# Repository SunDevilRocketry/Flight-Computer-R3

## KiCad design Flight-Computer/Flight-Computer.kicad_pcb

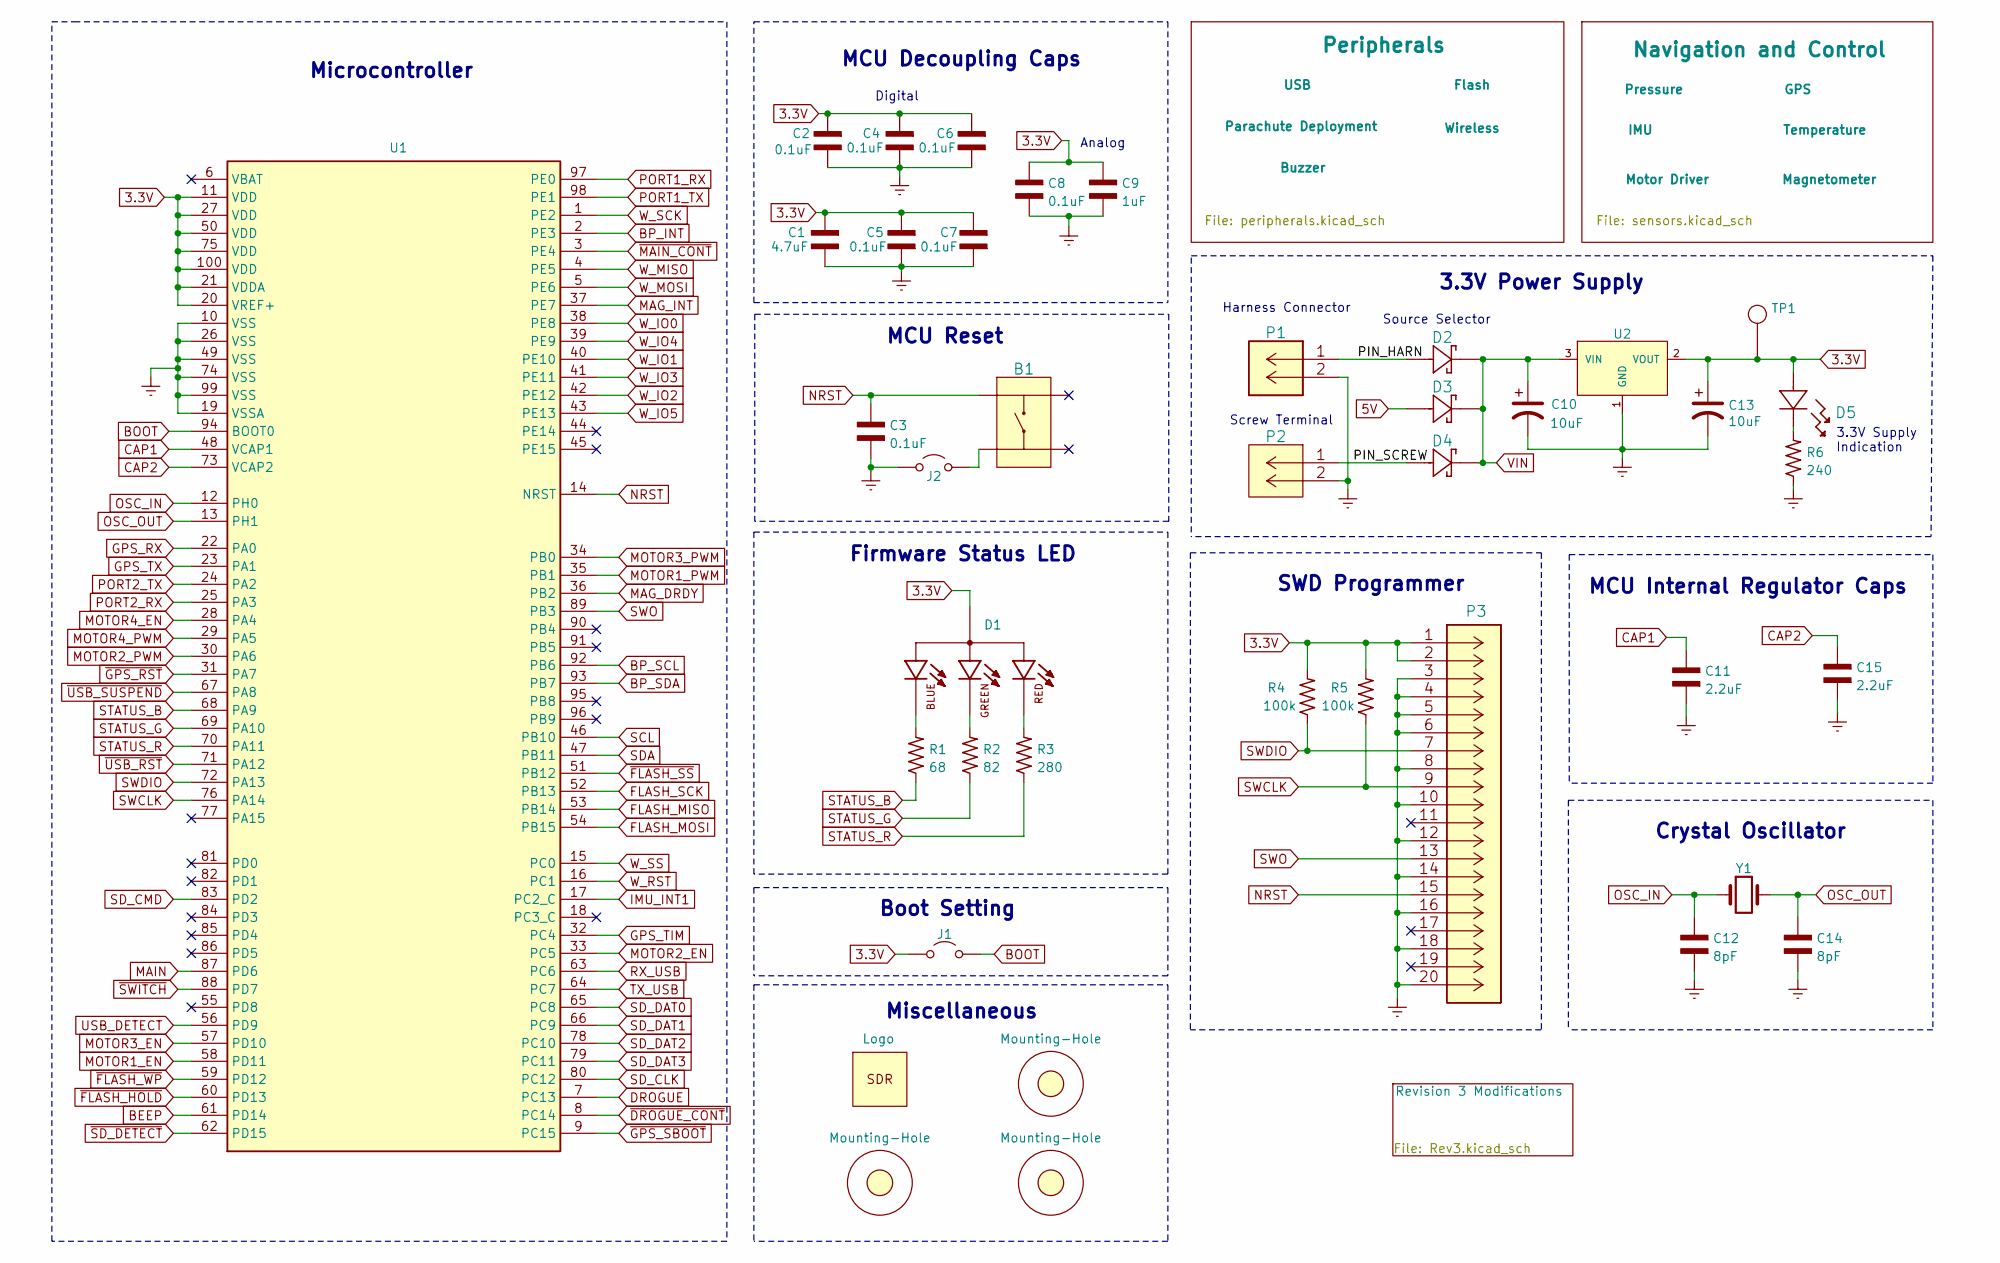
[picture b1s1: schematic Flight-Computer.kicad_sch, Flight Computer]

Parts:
B1: PTS647SM38SMTR2LFS
C1: 4.7uF; CAP_0603
C2, C3, C4, C5, C6, C7: 0.1uF; CAP_0603
C8: 0.1uF; C_0201_0603Metric
C9: 1uF; C_0201_0603Metric
C10, C13: 10uF; T491A106K010AT
C11, C15: 2.2uF; CAP_0603
C12, C14: 8pF; CAP_0603
D1: CLMVC-FKA-CL1D1L71BB7C3C3
D2, D3, D4: SM5819PL-TP
D5: SML-LX1206GC-TR
H1, H2, H3: Mounting-Hole; MountingHole_3mm
J1, J2: Jumper_NO; Jumper-NO
LOGO1: Logo
P1: 647676-2
P2: 1546551-2
P3: 3220-20-0200-00
R1: 68; RES_0603
R2: 82; RES_0603
R3: 280; RES_0603
R4, R5: 100k; RES_0603
R6: 240; RES_0603
TP1: TP
U1: STM32H750VBTx; STM32H750VBT6
U2: LMS8117AMP-3.3_NOPB; LMS8117AMP-3.3NOPB
Y1: ECS-240-18-33-JGN-TR

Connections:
3.3V: C1.1, C2.1, C4.1, C5.1, C6.1, C7.1, C8.1, C9.1, C13.1, D1.1, D5.2, J1.1 (A), P3.1, P3.2, R4.2, R5.2, TP1.1, U1.11 (VDD), U1.20 (VREF+), U1.21 (VDDA), U1.27 (VDD), U1.50 (VDD), U1.75 (VDD), U1.100 (VDD), U2.2 (VOUT); also elsewhere on the board
5V: D3.2; also elsewhere on the board
/PIN_HARN: D2.2, P1.1
/PIN_SCREW: D4.2, P2.1 (5)
BEEP: U1.61 (PD14); also elsewhere on the board
BOOT: J1.2 (B), U1.94 (BOOT0)
BP_INT: U1.2 (PE3); also elsewhere on the board
BP_SCL: U1.92 (PB6); also elsewhere on the board
BP_SDA: U1.93 (PB7); also elsewhere on the board
CAP1: C11.1, U1.48 (VCAP1)
CAP2: C15.1, U1.73 (VCAP2)
DROGUE: U1.7 (PC13); also elsewhere on the board
Earth: C1.2, C2.2, C3.2, C4.2, C5.2, C6.2, C7.2, C8.2, C9.2, C10.2, C11.2, C12.2, C13.2, C14.2, C15.2, J2.1 (A), P1.2, P2.2 (6), P3.3, P3.4, P3.5, P3.6, P3.8, P3.10, P3.12, P3.14, P3.16, P3.18, P3.20, R6.1, U1.10 (VSS), U1.19 (VSSA), U1.26 (VSS), U1.49 (VSS), U1.74 (VSS), U1.99 (VSS), U2.1 (GND); also elsewhere on the board
FLASH_MISO: U1.53 (PB14); also elsewhere on the board
FLASH_MOSI: U1.54 (PB15); also elsewhere on the board
FLASH_SCK: U1.52 (PB13); also elsewhere on the board
GPS_RX: U1.22 (PA0); also elsewhere on the board
GPS_TIM: U1.32 (PC4); also elsewhere on the board
GPS_TX: U1.23 (PA1); also elsewhere on the board
IMU_INT1: U1.17 (PC2_C); also elsewhere on the board
MAG_DRDY: U1.36 (PB2)
MAG_INT: U1.37 (PE7); also elsewhere on the board
MAIN: U1.87 (PD6); also elsewhere on the board
MOTOR1_EN: U1.58 (PD11); also elsewhere on the board
MOTOR1_PWM: U1.35 (PB1); also elsewhere on the board
MOTOR2_EN: U1.33 (PC5); also elsewhere on the board
MOTOR2_PWM: U1.30 (PA6); also elsewhere on the board
MOTOR3_EN: U1.57 (PD10); also elsewhere on the board
MOTOR3_PWM: U1.34 (PB0); also elsewhere on the board
MOTOR4_EN: U1.28 (PA4); also elsewhere on the board
MOTOR4_PWM: U1.29 (PA5); also elsewhere on the board
NRST: B1.3, C3.1, P3.15, U1.14 (NRST)
unnamed: D1.2, R1.2
unnamed: D1.3, R2.2
unnamed: D1.4, R3.2
unnamed: D5.1, R6.2
unnamed: B1.1, J2.2 (B)
OSC_IN: C12.1, U1.12 (PH0), Y1.1
OSC_OUT: C14.1, U1.13 (PH1), Y1.3
PORT1_RX: U1.97 (PE0); also elsewhere on the board
PORT1_TX: U1.98 (PE1); also elsewhere on the board
PORT2_RX: U1.25 (PA3); also elsewhere on the board
PORT2_TX: U1.24 (PA2); also elsewhere on the board
RX_USB: U1.63 (PC6); also elsewhere on the board
SCL: U1.46 (PB10); also elsewhere on the board
SDA: U1.47 (PB11); also elsewhere on the board
SD_CLK: U1.80 (PC12)
SD_CMD: U1.83 (PD2)
SD_DAT0: U1.65 (PC8)
SD_DAT1: U1.66 (PC9)
SD_DAT2: U1.78 (PC10)
SD_DAT3: U1.79 (PC11)
STATUS_B: R1.1, U1.68 (PA9)
STATUS_G: R2.1, U1.69 (PA10)
STATUS_R: R3.1, U1.70 (PA11)
SWCLK: P3.9, R5.1, U1.76 (PA14)
SWDIO: P3.7, R4.1, U1.72 (PA13)
SWO: P3.13, U1.89 (PB3)
TX_USB: U1.64 (PC7); also elsewhere on the board
USB_DETECT: U1.56 (PD9); also elsewhere on the board
VIN: C10.1, D2.1, D3.1, D4.1, U2.3 (VIN); also elsewhere on the board
W_IO0: U1.38 (PE8); also elsewhere on the board
W_IO1: U1.40 (PE10); also elsewhere on the board
W_IO2: U1.42 (PE12); also elsewhere on the board
W_IO3: U1.41 (PE11); also elsewhere on the board
W_IO4: U1.39 (PE9); also elsewhere on the board
W_IO5: U1.43 (PE13); also elsewhere on the board
W_MISO: U1.4 (PE5); also elsewhere on the board
W_MOSI: U1.5 (PE6); also elsewhere on the board
W_RST: U1.16 (PC1); also elsewhere on the board
W_SCK: U1.1 (PE2); also elsewhere on the board
W_SS: U1.15 (PC0); also elsewhere on the board
~DROGUE_CONT: U1.8 (PC14); also elsewhere on the board
~FLASH_HOLD: U1.60 (PD13); also elsewhere on the board
~FLASH_SS: U1.51 (PB12); also elsewhere on the board
~FLASH_WP: U1.59 (PD12); also elsewhere on the board
~GPS_RST: U1.31 (PA7); also elsewhere on the board
~GPS_SBOOT: U1.9 (PC15); also elsewhere on the board
~MAIN_CONT: U1.3 (PE4); also elsewhere on the board
~SD_DETECT: U1.62 (PD15)
~SWITCH: U1.88 (PD7); also elsewhere on the board
~USB_RST: U1.71 (PA12); also elsewhere on the board
~USB_SUSPEND: U1.67 (PA8); also elsewhere on the board

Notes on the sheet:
Crystal Oscillator
3.3V Power Supply
MCU Internal Regulator Caps
MCU Reset
Firmware Status LED
3.3V Supply Indication
Source Selector
MCU Decoupling Caps
Boot Setting
Miscellaneous
Analog
Screw Terminal
Microcontroller
Harness Connector
Digital
SWD Programmer

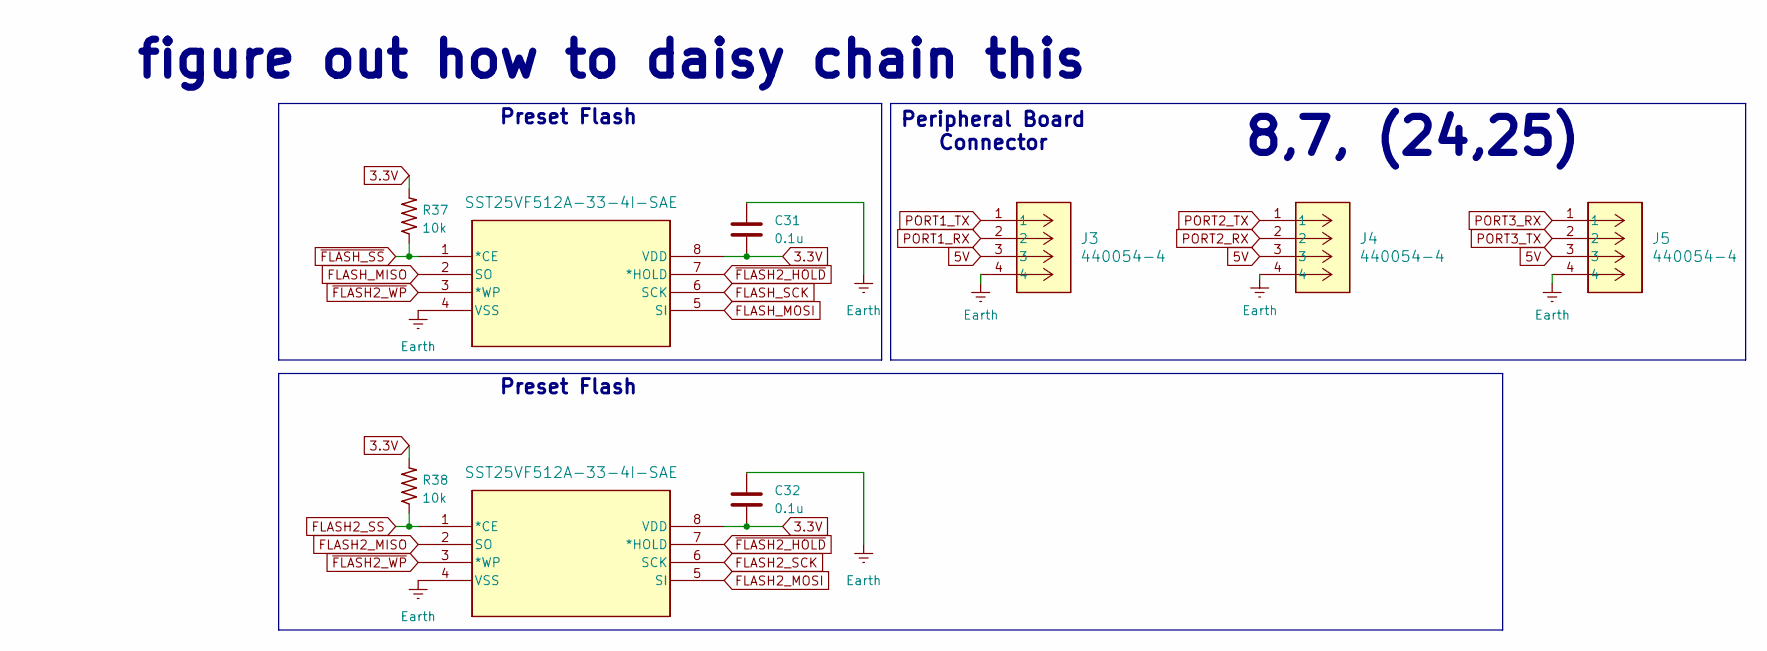
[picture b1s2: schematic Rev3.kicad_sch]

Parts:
C31, C32: 0.1u; C_0603_1608Metric
J3, J4, J5: 440054-4; CONN_440054-4_TEC
R37, R38: 10k; RES_0603
U14, U15: SST25VF512A-33-4I-SAE; SOIC8_SA_SST_MCH

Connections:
3.3V: C31.2, C32.2, R37.2, R38.2, U14.8 (VDD), U15.8 (VDD); also elsewhere on the board
5V: J3.3, J4.3, J5.3; also elsewhere on the board
Earth: C31.1, C32.1, J3.4, J4.4, J5.4, U14.4 (VSS), U15.4 (VSS); also elsewhere on the board
FLASH2_MISO: U14.2 (SO)
FLASH2_MOSI: U14.5 (SI)
FLASH2_SCK: U14.6 (SCK)
FLASH2_SS: R38.1, U14.1 (*CE)
FLASH_MISO: U15.2 (SO); also elsewhere on the board
FLASH_MOSI: U15.5 (SI); also elsewhere on the board
FLASH_SCK: U15.6 (SCK); also elsewhere on the board
PORT1_RX: J3.2; also elsewhere on the board
PORT1_TX: J3.1; also elsewhere on the board
PORT2_RX: J4.2; also elsewhere on the board
PORT2_TX: J4.1; also elsewhere on the board
PORT3_RX: J5.1
PORT3_TX: J5.2
~FLASH2_HOLD: U14.7 (*HOLD), U15.7 (*HOLD)
~FLASH2_WP: U14.3 (*WP), U15.3 (*WP)
~FLASH_SS: R37.1, U15.1 (*CE); also elsewhere on the board

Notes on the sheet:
figure out how to daisy chain this
8,7, (24,25)
Preset Flash
Peripheral Board Connector

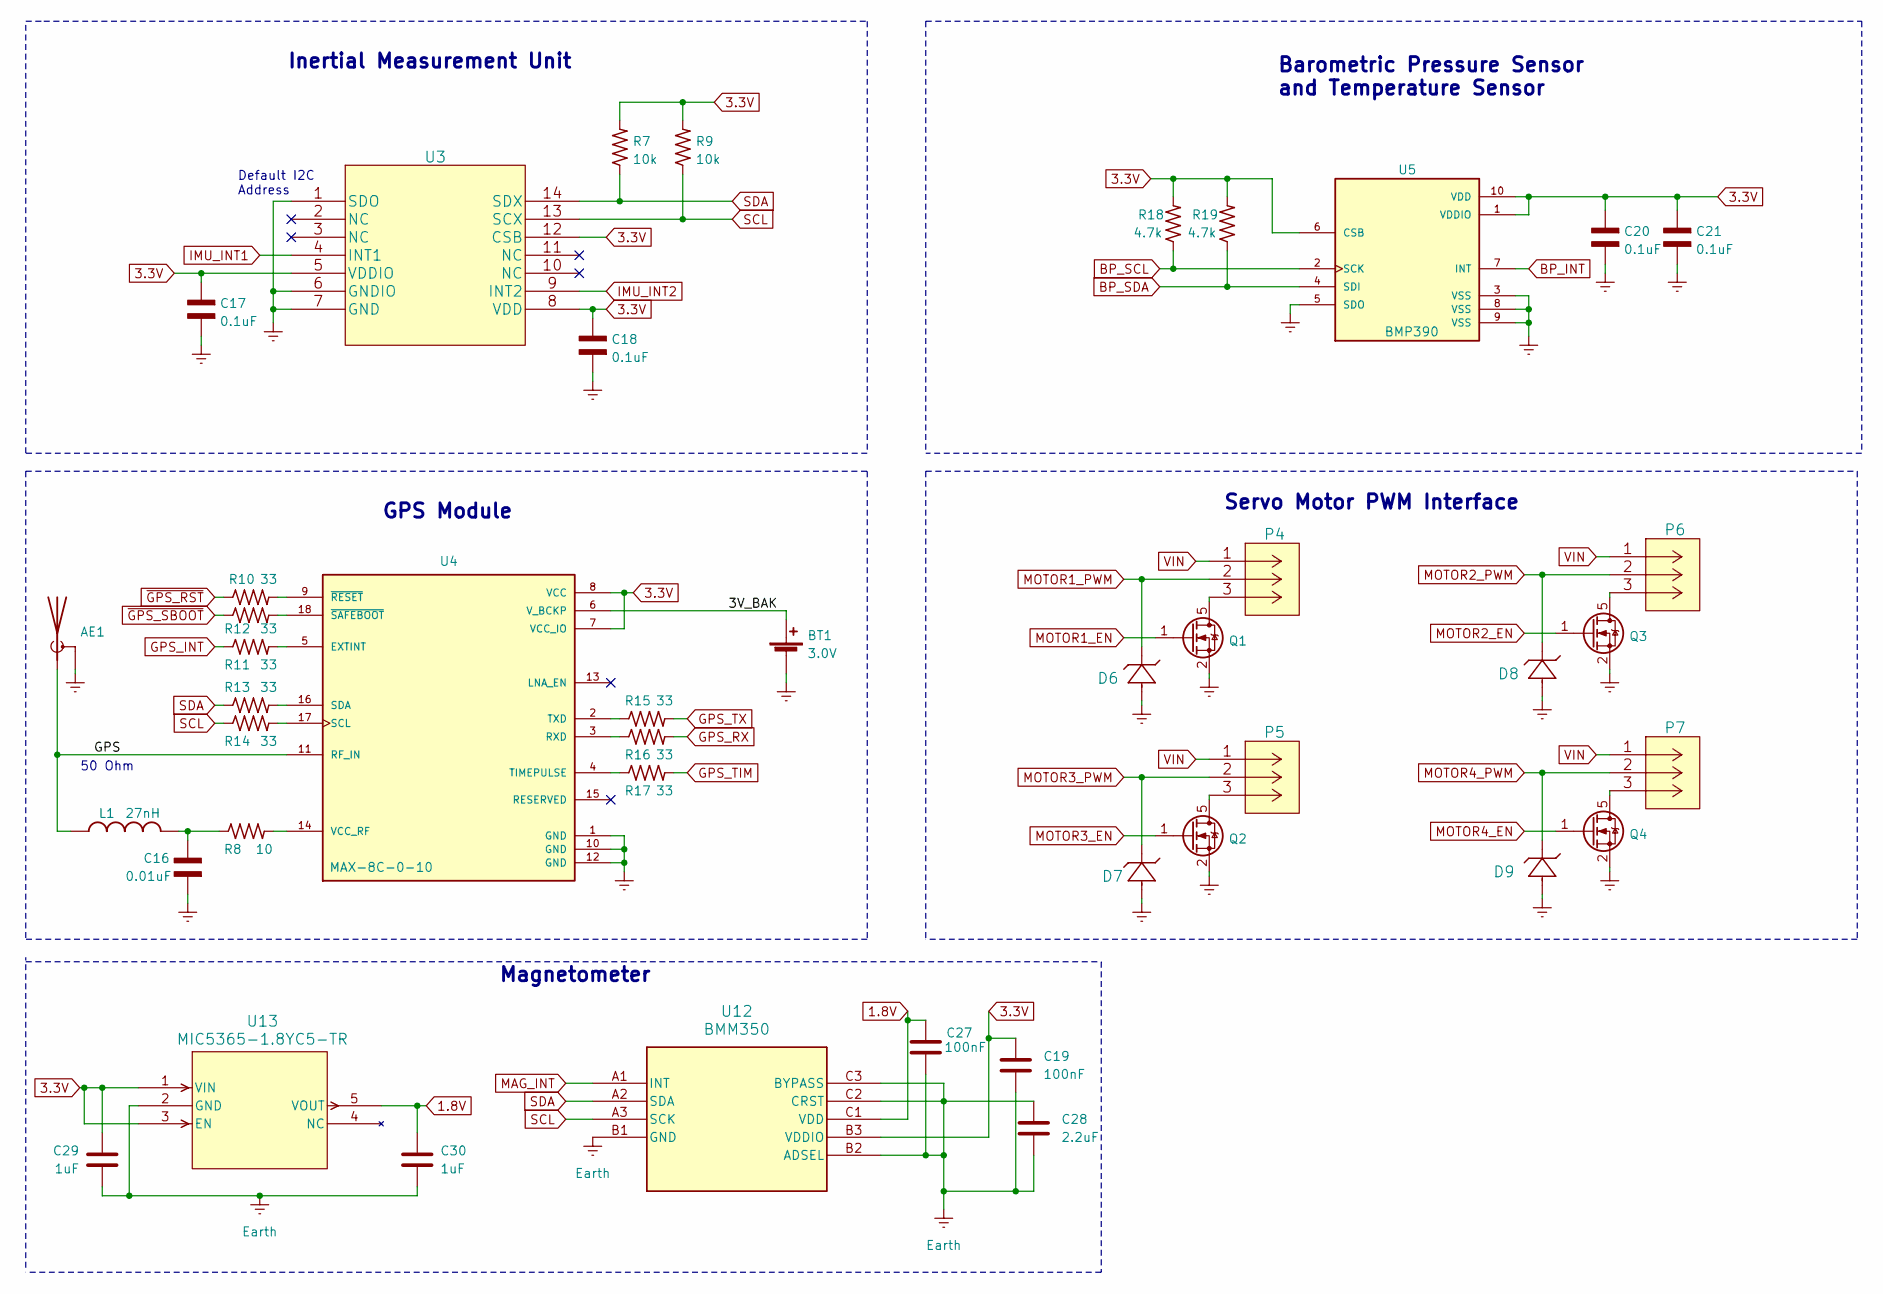
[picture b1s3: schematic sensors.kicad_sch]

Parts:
AE1: 0734120110; 73412-0110
BT1: MS614SE-FL28E; MS621FE-FL11E; Voltage 3.0V
C16: 0.01uF; CAP_0603
C17, C20, C21: 0.1uF; CAP_0603
C18: 0.1uF; C_0201_0603Metric
C19, C27: 100nF; C_0201_0603Metric
C28: 2.2uF; C_0201_0603Metric
C29, C30: 1uF; C_0402_1005Metric
D6, D7, D8, D9: MM3Z3V3B
L1: 27nH; L-07C27NJV6T
P4, P5, P6, P7: 440054-3
Q1, Q2, Q3, Q4: QS5U17TR
R7, R9: 10k; RES_0603
R8: 10; RES_0603
R10, R11, R12, R13, R14, R15, R16, R17: 33; RES_0603
R18, R19: 4.7k; RES_0603
U3: BMI323
U4: MAX-8C-0-10; MAX-8C-0
U5: BMP390
U12: BMM350; BGA9_BMM350_BOS
U13: MIC5365-1.8YC5-TR; SC-70_C5_MCH-L

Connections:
1.8V: C27.1, C30.1, U12.C1 (VDD), U13.5 (VOUT); also elsewhere on the board
3.3V: C17.1, C18.1, C19.1, C20.1, C21.1, C29.1, R7.2, R9.2, R18.2, R19.2, U3.5 (VDDIO), U3.8 (VDD), U3.12 (CSB), U4.7 (VCC_IO), U4.8 (VCC), U5.1 (VDDIO), U5.6 (CSB), U5.10 (VDD), U12.B3 (VDDIO), U13.1 (VIN), U13.3 (EN); also elsewhere on the board
/Navigation and Control/3V_BAK: BT1.1 (+), U4.6 (V_BCKP)
/Navigation and Control/GPS: AE1.1 (A), L1.1, U4.11 (RF_IN)
BP_INT: U5.7 (INT); also elsewhere on the board
BP_SCL: R18.1, U5.2 (SCK); also elsewhere on the board
BP_SDA: R19.1, U5.4 (SDI); also elsewhere on the board
Earth: AE1.2 (Shield), BT1.2 (-), C16.2, C17.2, C18.2, C19.2, C20.2, C21.2, C27.2, C28.1, C28.2, C29.2, C30.2, D6.2, D7.2, D8.2, D9.2, Q1.2 (S), Q2.2 (S), Q3.2 (S), Q4.2 (S), U3.1 (SDO), U3.6 (GNDIO), U3.7 (GND), U4.1 (GND), U4.10 (GND), U4.12 (GND), U5.3 (VSS), U5.5 (SDO), U5.8 (VSS), U5.9 (VSS), U12.B1 (GND), U12.B2 (ADSEL), U12.C2 (CRST), U12.C3 (BYPASS), U13.2 (GND); also elsewhere on the board
GPS_INT: R12.1
GPS_RX: R16.2; also elsewhere on the board
GPS_TIM: R17.2; also elsewhere on the board
GPS_TX: R15.2; also elsewhere on the board
IMU_INT1: U3.4 (INT1); also elsewhere on the board
IMU_INT2: U3.9 (INT2)
MAG_INT: U12.A1 (INT); also elsewhere on the board
MOTOR1_EN: Q1.1 (G); also elsewhere on the board
MOTOR1_PWM: D6.1, P4.2 (GND); also elsewhere on the board
MOTOR2_EN: Q3.1 (G); also elsewhere on the board
MOTOR2_PWM: D8.1, P6.2 (GND); also elsewhere on the board
MOTOR3_EN: Q2.1 (G); also elsewhere on the board
MOTOR3_PWM: D7.1, P5.2 (GND); also elsewhere on the board
MOTOR4_EN: Q4.1 (G); also elsewhere on the board
MOTOR4_PWM: D9.1, P7.2 (GND); also elsewhere on the board
unnamed: C16.1, L1.2, R8.1
unnamed: P4.3, Q1.5 (D)
unnamed: P5.3, Q2.5 (D)
unnamed: P6.3, Q3.5 (D)
unnamed: P7.3, Q4.5 (D)
unnamed: R12.2, U4.5 (EXTINT)
unnamed: R16.1, U4.3 (RXD)
unnamed: R14.2, U4.17 (SCL)
unnamed: R13.2, U4.16 (SDA)
unnamed: R17.1, U4.4 (TIMEPULSE)
unnamed: R15.1, U4.2 (TXD)
unnamed: R8.2, U4.14 (VCC_RF)
unnamed: R10.2, U4.9 (~RESET)
unnamed: R11.2, U4.18 (~SAFEBOOT)
SCL: R9.1, R14.1, U3.13 (SCX), U12.A3 (SCK); also elsewhere on the board
SDA: R7.1, R13.1, U3.14 (SDX), U12.A2 (SDA); also elsewhere on the board
VIN: P4.1 (+12V), P5.1 (+12V), P6.1 (+12V), P7.1 (+12V); also elsewhere on the board
~GPS_RST: R10.1; also elsewhere on the board
~GPS_SBOOT: R11.1; also elsewhere on the board

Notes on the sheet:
Default I2C Address
Servo Motor PWM Interface
50 Ohm
Magnetometer
GPS Module
Barometric Pressure Sensor and Temperature Sensor
Inertial Measurement Unit

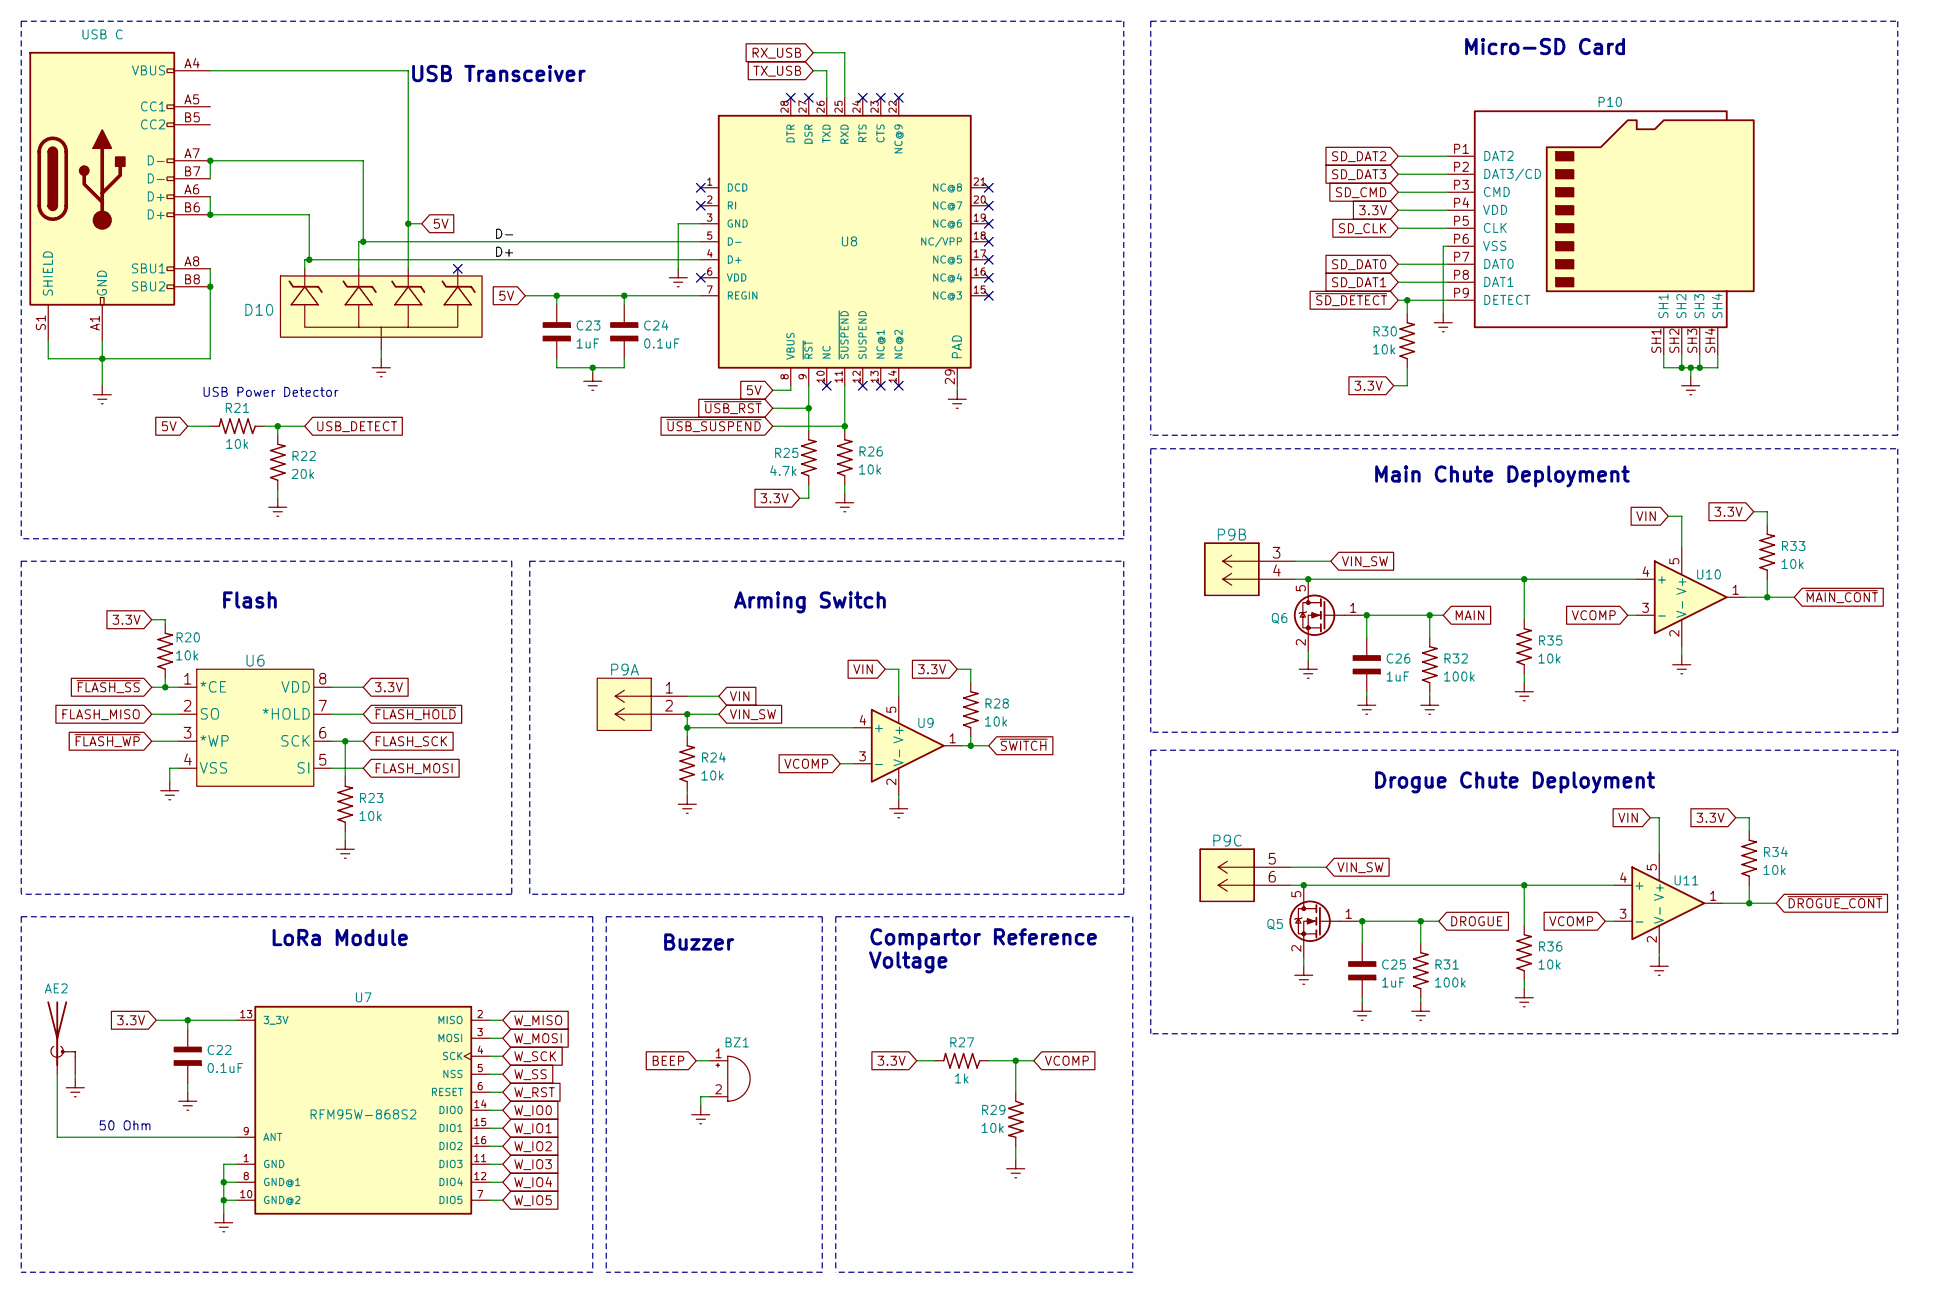
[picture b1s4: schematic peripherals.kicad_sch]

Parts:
AE2: 142-0701-851
BZ1: AT-1438-TWT-R
C22: 0.1uF; C_0201_0603Metric
C23, C25, C26: 1uF; CAP_0603
C24: 0.1uF; CAP_0603
D10: SP0504BAHTG
J6: USB C
P9: 1984659
P10: Micro_SD_Card; MEM2075-00-140-01-A
Q5, Q6: QS5U17TR
R20, R21, R23, R24, R26, R28, R29, R30, R33, R34, R35, R36: 10k; RES_0603
R22: 20k; RES_0603
R25: 4.7k; RES_0603
R27: 1k; RES_0603
R31, R32: 100k; RES_0603
U6: SST25VF040B-50-4I-S2AE-T
U7: RFM95W-868S2; RFM95
U8: CP2102-GMR(QFN28); CP2012-GMR; MPN CP2102-GMR
U9, U10, U11: TS391IYLT

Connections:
3.3V: C22.1, P10.P4 (VDD), R20.2, R25.1, R27.2, R28.2, R30.1, R33.2, R34.2, U6.8 (VDD), U7.13 (3_3V); also elsewhere on the board
5V: C23.1, C24.1, D10.4, J6.A4 (VBUS), J6.A9 (VBUS), J6.B4 (VBUS), J6.B9 (VBUS), R21.2, U8.7 (REGIN), U8.8 (VBUS); also elsewhere on the board
/Peripherals/D+: D10.1, J6.A6 (D+), J6.B6 (D+), U8.4 (D+); also elsewhere on the board
/Peripherals/D-: D10.3, J6.A7 (D-), J6.B7 (D-), U8.5 (D-); also elsewhere on the board
BEEP: BZ1.1 (-); also elsewhere on the board
DROGUE: C25.1, Q5.1 (G), R31.2; also elsewhere on the board
Earth: AE2.2 (Shield), BZ1.2 (+), C22.2, C23.2, C24.2, C25.2, C26.2, D10.2, J6.A1 (GND), J6.A8 (SBU1), J6.A12 (GND), J6.B1 (GND), J6.B8 (SBU2), J6.B12 (GND), J6.S1 (SHIELD), P10.P6 (VSS), P10.SH1, P10.SH2, P10.SH3, P10.SH4, Q5.2 (S), Q6.2 (S), R22.1, R23.1, R24.1, R26.1, R29.2, R31.1, R32.1, R35.1, R36.1, U6.4 (VSS), U7.1 (GND), U7.8 (GND@1), U7.10 (GND@2), U8.3 (GND), U8.29 (PAD), U9.2 (V-), U10.2 (V-), U11.2 (V-); also elsewhere on the board
FLASH_MISO: U6.2 (SO); also elsewhere on the board
FLASH_MOSI: U6.5 (SI); also elsewhere on the board
FLASH_SCK: R23.2, U6.6 (SCK); also elsewhere on the board
MAIN: C26.1, Q6.1 (G), R32.2; also elsewhere on the board
unnamed: AE2.1 (A), U7.9 (ANT)
unnamed: P9.4 (6), Q6.5 (D), R35.2, U10.4 (+)
unnamed: P10.P9 (DETECT), R30.2
unnamed: P9.6, Q5.5 (D), R36.2, U11.4 (+)
RX_USB: U8.25 (RXD); also elsewhere on the board
TX_USB: U8.26 (TXD); also elsewhere on the board
USB_DETECT: R21.1, R22.2; also elsewhere on the board
VCOMP: R27.1, R29.1, U9.3 (-), U10.3 (-), U11.3 (-)
VIN: P9.1 (5), U9.5 (V+), U10.5 (V+), U11.5 (V+); also elsewhere on the board
VIN_SW: P9.2 (6), P9.3 (5), P9.5, R24.2, U9.4 (+)
W_IO0: U7.14 (DIO0); also elsewhere on the board
W_IO1: U7.15 (DIO1); also elsewhere on the board
W_IO2: U7.16 (DIO2); also elsewhere on the board
W_IO3: U7.11 (DIO3); also elsewhere on the board
W_IO4: U7.12 (DIO4); also elsewhere on the board
W_IO5: U7.7 (DIO5); also elsewhere on the board
W_MISO: U7.2 (MISO); also elsewhere on the board
W_MOSI: U7.3 (MOSI); also elsewhere on the board
W_RST: U7.6 (RESET); also elsewhere on the board
W_SCK: U7.4 (SCK); also elsewhere on the board
W_SS: U7.5 (NSS); also elsewhere on the board
~DROGUE_CONT: R34.1, U11.1; also elsewhere on the board
~FLASH_HOLD: U6.7 (*HOLD); also elsewhere on the board
~FLASH_SS: R20.1, U6.1 (*CE); also elsewhere on the board
~FLASH_WP: U6.3 (*WP); also elsewhere on the board
~MAIN_CONT: R33.1, U10.1; also elsewhere on the board
~SWITCH: R28.1, U9.1; also elsewhere on the board
~USB_RST: R25.2, U8.9 (~RST); also elsewhere on the board
~USB_SUSPEND: R26.2, U8.11 (~SUSPEND); also elsewhere on the board

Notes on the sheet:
Micro-SD Card
Compartor Reference Voltage
USB Power Detector
Arming Switch
50 Ohm
Drogue Chute Deployment
Buzzer
Flash
USB Transceiver
Main Chute Deployment
LoRa Module

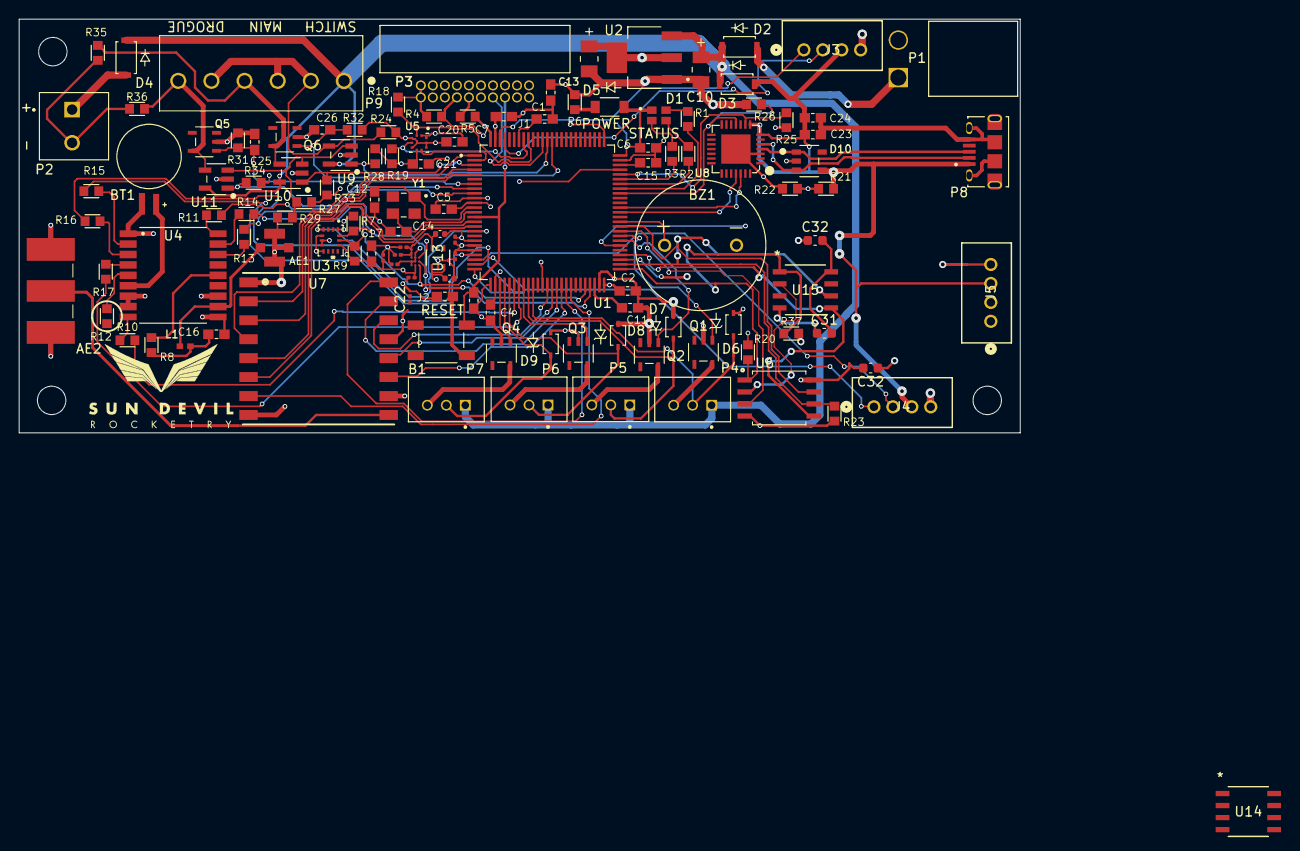
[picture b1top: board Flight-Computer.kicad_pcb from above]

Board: 4 copper layers, 105.7 x 43.7 mm, 127 parts (1 on the bottom side), 101 nets.

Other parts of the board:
C30#2: 1uF; C_0402_1005Metric
C32#2: 0.1u; C_0603_1608Metric
P8: USB; 10118194-0001LF

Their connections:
1.8V: C30#2.1; also elsewhere on the board
3.3V: C32#2.2; also elsewhere on the board
5V: P8.1 (VCC); also elsewhere on the board
/Peripherals/D+: P8.3 (D+); also elsewhere on the board
/Peripherals/D-: P8.2 (D-); also elsewhere on the board
Earth: C30#2.2, C32#2.1, P8.5 (GND), P8.S1 (SHIELD), P8.S2 (SHIELD); also elsewhere on the board

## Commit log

2025-02-21 PUART and PFlash
    Added Peripheral board UART and Preset Flash
2025-02-21 test
2025-02-26 New Flash/4x UART
    Added Microchip Technologies Flash and 3 more UART peripheral connectors
2025-03-03 American PFLASH/PUART
    Made to appease the American mind (Changed symbols and orientations)
2025-03-03 LDO update
    Changed buck 1.8V converter to LDO
2025-03-28 Ports
    Added 2 UART ports for connectivity, expanded board
2025-04-04 SPI Flash Daisy chain
    need to review and likely rewire the daisy chain
2025-09-23 most up to date rev 2.5 files
    third connector (where micro sd used to be) does not have tx3 pins connected (pin outs needed in order to wire)

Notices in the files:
parts and their libraries:
Copyright 2021 Accelerated Designs. All rights reserved.
